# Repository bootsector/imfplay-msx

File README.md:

# imfplay-msx
IMF Player for MSX

This is a small utility for playing IMF files (OPL2) on the MSX.

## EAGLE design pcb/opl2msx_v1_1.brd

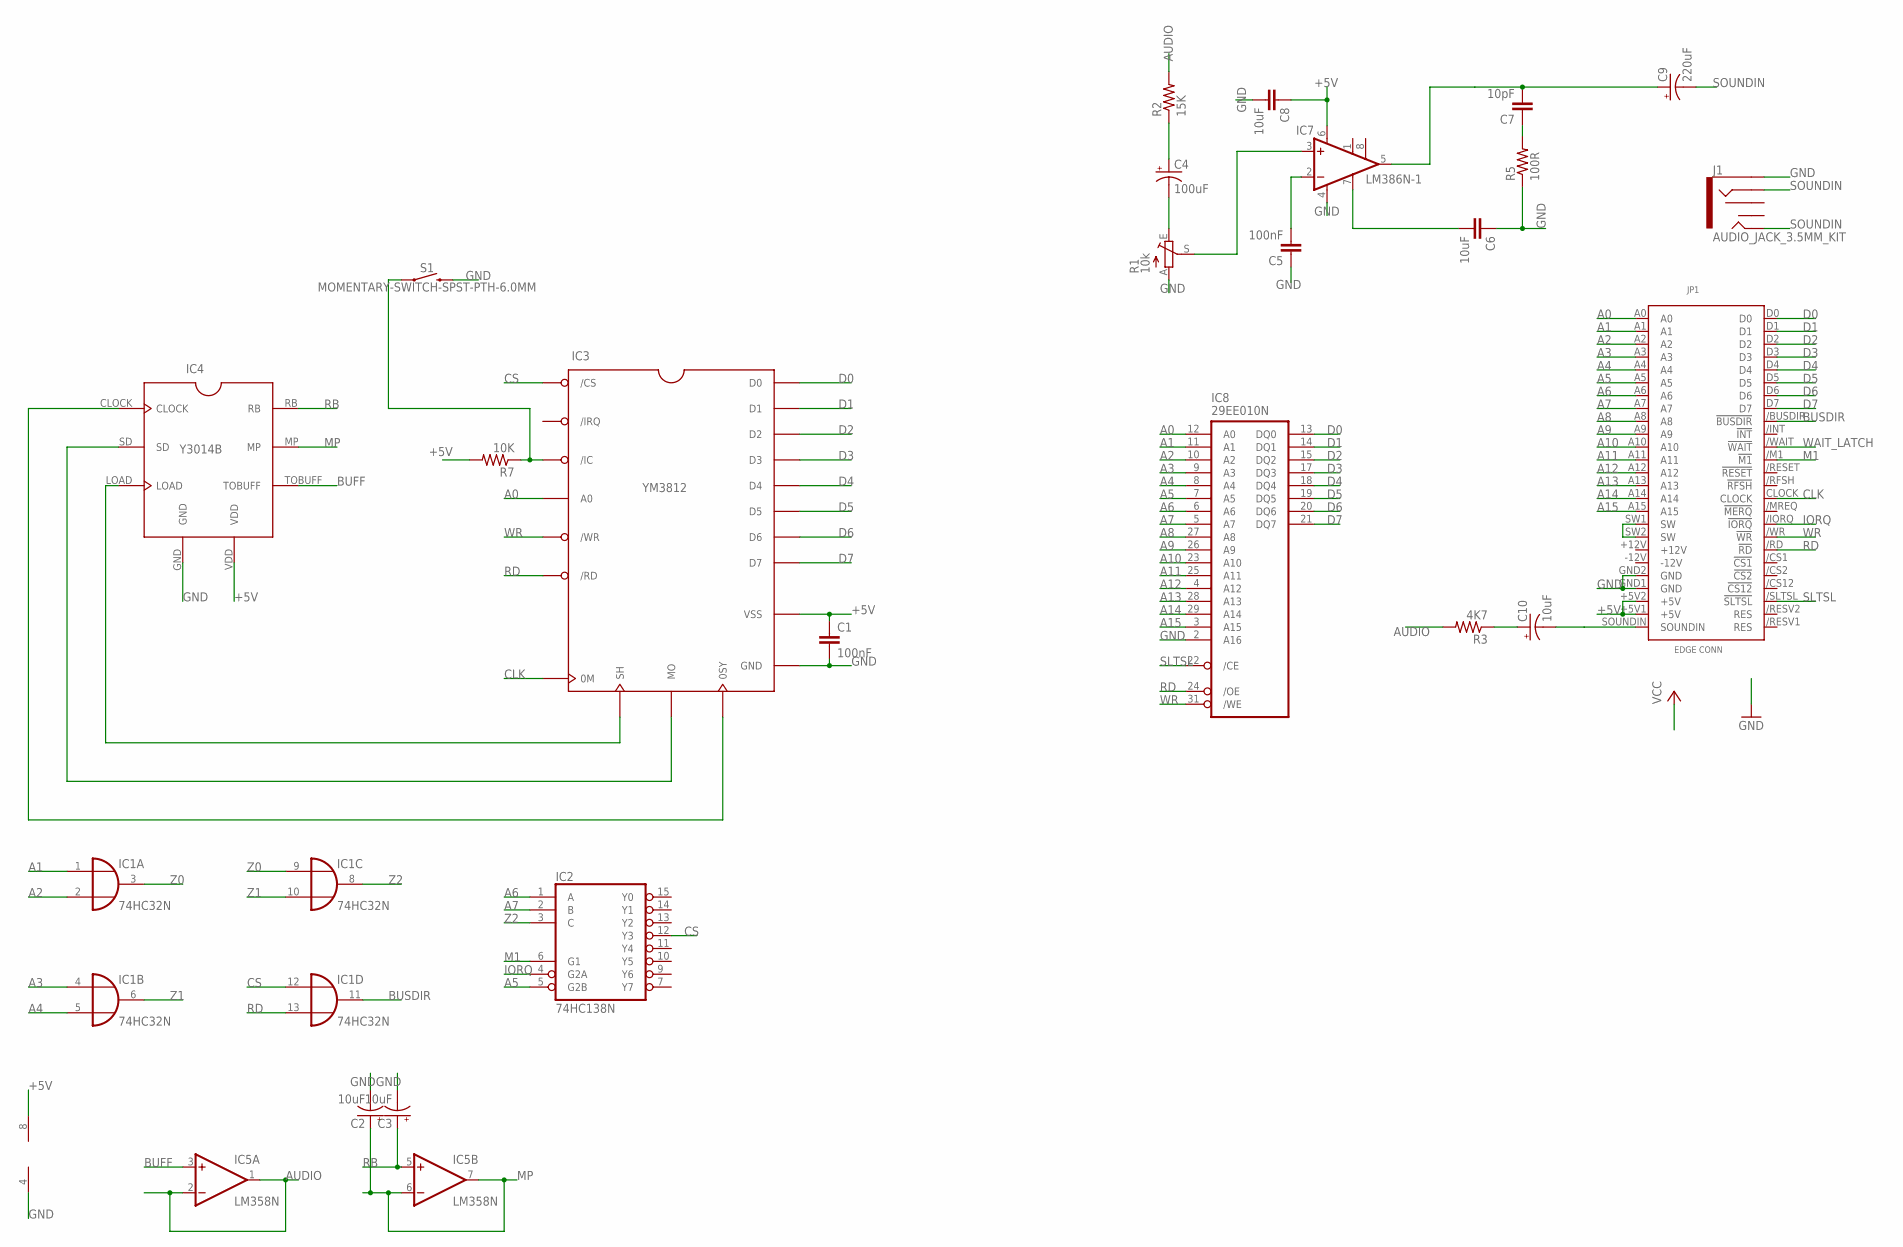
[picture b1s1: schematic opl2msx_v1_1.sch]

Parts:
C1, C5: 100nF; C050-024X044
C2, C3, C10: 10uF; E2,5-6
C4: 100uF; E2,5-6
C6, C8: 10uF; C050-024X044
C7: 10pF; C050-024X044
C9: 220uF; E2,5-6
IC1: 74HC32N; DIL14
IC2: 74HC138N; DIL16
IC3: YM3812
IC4: Y3014B; YM3014B
IC5: LM358N; DIL08
IC7: LM386N-1; DIL08
IC8: 29EE010N; DIL32-6
J1: AUDIO_JACK_3.5MM_KIT; AUDIO-JACK-KIT
JP1: MSXCART; PATOLA-MSX-SEEED
R1: 10k; CA6V
R2: 15K; 0207/10
R3: 4K7; 0207/10
R5: 100R; 0207/10
R7: 10K; 0207/10
S1: MOMENTARY-SWITCH-SPST-PTH-6.0MM; TACTILE_SWITCH_PTH_6.0MM

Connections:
+5V: C1.1, C8.1, IC1.14 (VCC), IC2.16 (VCC), IC3.VSS, IC4.VDD, IC5.8 (V+), IC7.6 (VS), IC8.32 (VCC), JP1.+5V1 (+5V), JP1.+5V2 (+5V), R7.2
A0: IC3.A0, IC8.12 (A0), JP1.A0
A1: IC1.1 (I0), IC8.11 (A1), JP1.A1
A2: IC1.2 (I1), IC8.10 (A2), JP1.A2
A3: IC1.4 (I0), IC8.9 (A3), JP1.A3
A4: IC1.5 (I1), IC8.8 (A4), JP1.A4
A5: IC2.5 (G2B), IC8.7 (A5), JP1.A5
A6: IC2.1 (A), IC8.6 (A6), JP1.A6
A7: IC2.2 (B), IC8.5 (A7), JP1.A7
A8: IC8.27 (A8), JP1.A8
A9: IC8.26 (A9), JP1.A9
A10: IC8.23 (A10), JP1.A10
A11: IC8.25 (A11), JP1.A11
A12: IC8.4 (A12), JP1.A12
A13: IC8.28 (A13), JP1.A13
A14: IC8.29 (A14), JP1.A14
A15: IC8.3 (A15), JP1.A15
AUDIO: IC5.1 (OUT), IC5.2 (-IN), R2.2, R3.2
BUFF: IC4.TOBUFF, IC5.3 (+IN)
BUSDIR: IC1.11 (O), JP1./BUSDIR (!BUSDIR)
CLK: IC3.0M, JP1.CLOCK
CS: IC1.12 (I0), IC2.12 (Y3), IC3./CS
D0: IC3.D0, IC8.13 (DQ0), JP1.D0
D1: IC3.D1, IC8.14 (DQ1), JP1.D1
D2: IC3.D2, IC8.15 (DQ2), JP1.D2
D3: IC3.D3, IC8.17 (DQ3), JP1.D3
D4: IC3.D4, IC8.18 (DQ4), JP1.D4
D5: IC3.D5, IC8.19 (DQ5), JP1.D5
D6: IC3.D6, IC8.20 (DQ6), JP1.D6
D7: IC3.D7, IC8.21 (DQ7), JP1.D7
GND: C1.2, C2.-, C3.-, C5.1, C6.1, C8.2, IC1.7 (GND), IC2.8 (GND), IC3.GND, IC4.GND, IC5.4 (V-), IC7.4 (GND), IC8.2 (A16), IC8.16 (GND), J1.SLEEVE, JP1.GND1 (GND), JP1.GND2 (GND), R1.A, R5.1, S1.3 (2)
IORQ: IC2.4 (G2A), JP1./IORQ (!IORQ)
M1: IC2.6 (G1), JP1./M1 (!M1)
MP: C2.+, IC4.MP, IC5.6 (-IN), IC5.7 (OUT)
unnamed: C4.+, R2.1
unnamed: C6.2, IC7.7 (BYPASS)
unnamed: C4.-, R1.E
unnamed: IC7.3 (+IN), R1.S
unnamed: C5.2, IC7.2 (-IN)
unnamed: C10.-, JP1.SOUNDIN
unnamed: C10.+, R3.1
unnamed: C7.2, C9.+, IC7.5 (OUT)
unnamed: C7.1, R5.2
unnamed: IC3.SH, IC4.LOAD
unnamed: IC3.MO, IC4.SD
unnamed: IC3.0SY, IC4.CLOCK
unnamed: IC3./IC, R7.1, S1.1
unnamed: JP1.SW1 (SW), JP1.SW2 (SW)
RB: C3.+, IC4.RB, IC5.5 (+IN)
RD: IC1.13 (I1), IC3./RD, IC8.24 (/OE), JP1./RD (!RD)
SLTSL: IC8.22 (/CE), JP1./SLTSL (!SLTSL)
SOUNDIN: C9.-, J1.RING, J1.TIP
WAIT_LATCH: JP1./WAIT (!WAIT)
WR: IC3./WR, IC8.31 (/WE), JP1./WR (!WR)
Z0: IC1.3 (O), IC1.9 (I0)
Z1: IC1.6 (O), IC1.10 (I1)
Z2: IC1.8 (O), IC2.3 (C)

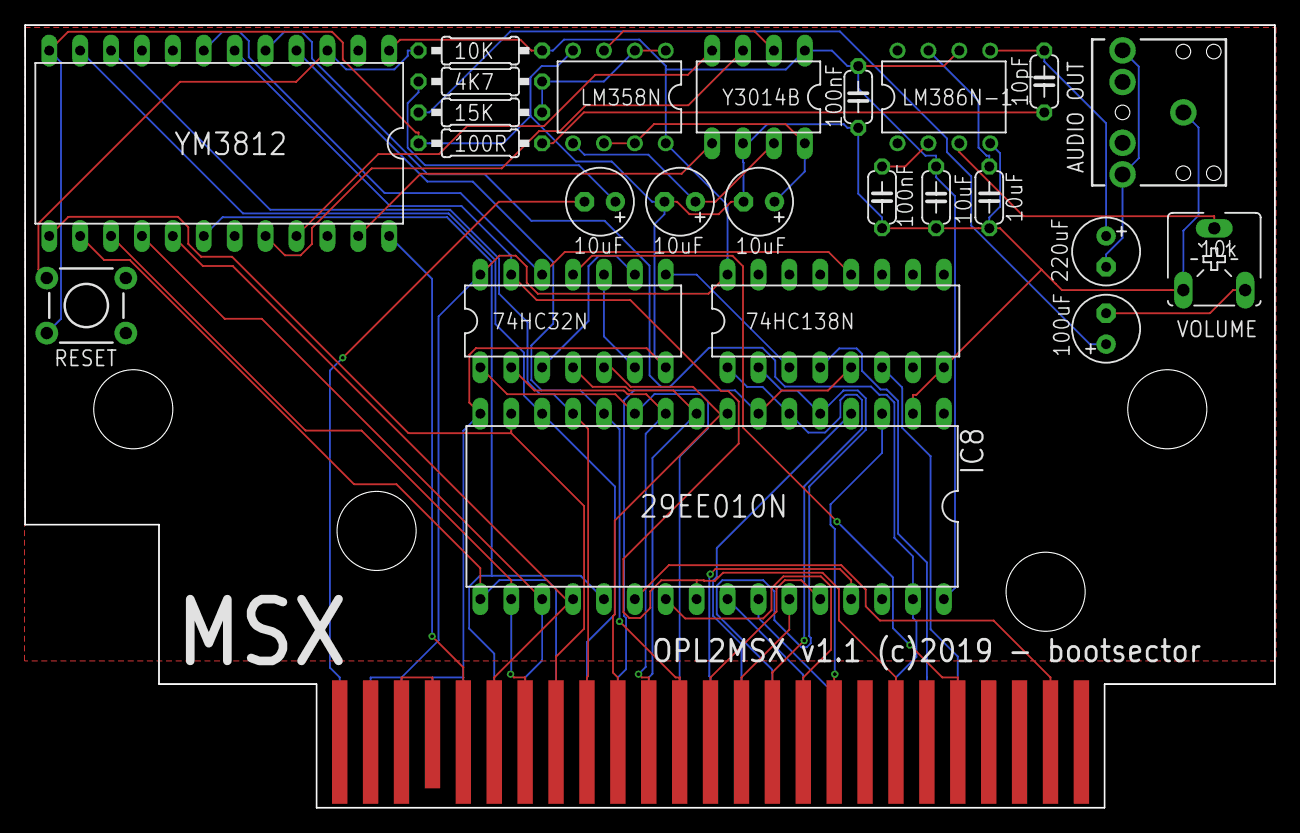
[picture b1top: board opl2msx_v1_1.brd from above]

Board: 2 copper layers, 102.7 x 64.3 mm, 25 parts (0 on the bottom side), 56 nets.

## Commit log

2017-12-31 Got rid of float rounding routines (too slow). Fixed _msx_wait_jiffies so it does not hang in there if a zero is passed as the parameter
2017-12-31 Simplified delay function. Added percentage for file loading process
2019-02-11 Added OPL2MSX PCB eagle files
2019-02-14 Added OPL2MSX PCB schematics version 1.1 (untested)
2019-02-14 Fixed PCB version 1.1. Removed unused 7404 IC
2019-02-14 Updated PCB v1.1 layout
2019-03-03 Using sdobjcopy instead of gobjcopy
2019-03-06 Updated Makefiles for SDCC 3.8.0

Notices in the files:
pcb/opl2msx_v1_1.brd:
OPL2MSX v1.1 (c)2019 - bootsector
parts and their libraries:
SparkFun-Connectors: Licensing: Creative Commons ShareAlike 4.0 International - https://creativecommons.org/licenses/by-sa/4.0
